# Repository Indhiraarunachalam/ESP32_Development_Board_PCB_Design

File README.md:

# ESP32 Development Board PCB Design

## Overview

This project presents the design of a custom ESP32 Development Board PCB developed using KiCad. The board includes USB connectivity, a regulated 3.3V power supply, reset and boot circuits, and a DHT22 temperature and humidity sensor interface. The design follows the complete PCB development workflow from schematic capture to PCB layout and Gerber generation.

---

## Features

- ESP32 Development Board
- DHT22 Temperature & Humidity Sensor Interface
- USB Power Input
- 3.3V Voltage Regulator
- Reset (EN) Button
- Boot Button
- Status LED
- Two-Layer PCB Design

---

## Software Used

- KiCad

---

## Hardware Components

- ESP32-WROOM Module
- DHT22 Sensor
- USB Connector
- AMS1117-3.3V Voltage Regulator
- Push Buttons
- LEDs
- Resistors
- Capacitors
- Transistor

---

## Design Flow

1. Schematic Design
2. ERC Verification
3. PCB Layout
4. Component Placement
5. Routing
6. DRC Verification
7. Gerber Generation

---

## Design Verification

- ERC Passed ✅
- DRC Passed ✅
- Gerber Files Generated Successfully ✅
- Ready for PCB Fabrication ✅

---

## Repository Structure

```
ESP32-Development-Board-PCB-Design
│
├── ESP32_DHT.kicad_sch
├── ESP32_DHT.kicad_pcb
├── README.md
│
├── Gerber/
│
└── Images/
    ├── Schematic.png
    ├── PCB_Toplayer.png
    └── PCB_Bottomlayer.png
```

---

## Project Images

### Schematic

### PCB Layout - Top Layer

### PCB Layout - Bottom Layer

---

## Author

**Indhira A**

Electronics and Communication Engineering Student

Interested in PCB Design, Embedded Systems and IoT.

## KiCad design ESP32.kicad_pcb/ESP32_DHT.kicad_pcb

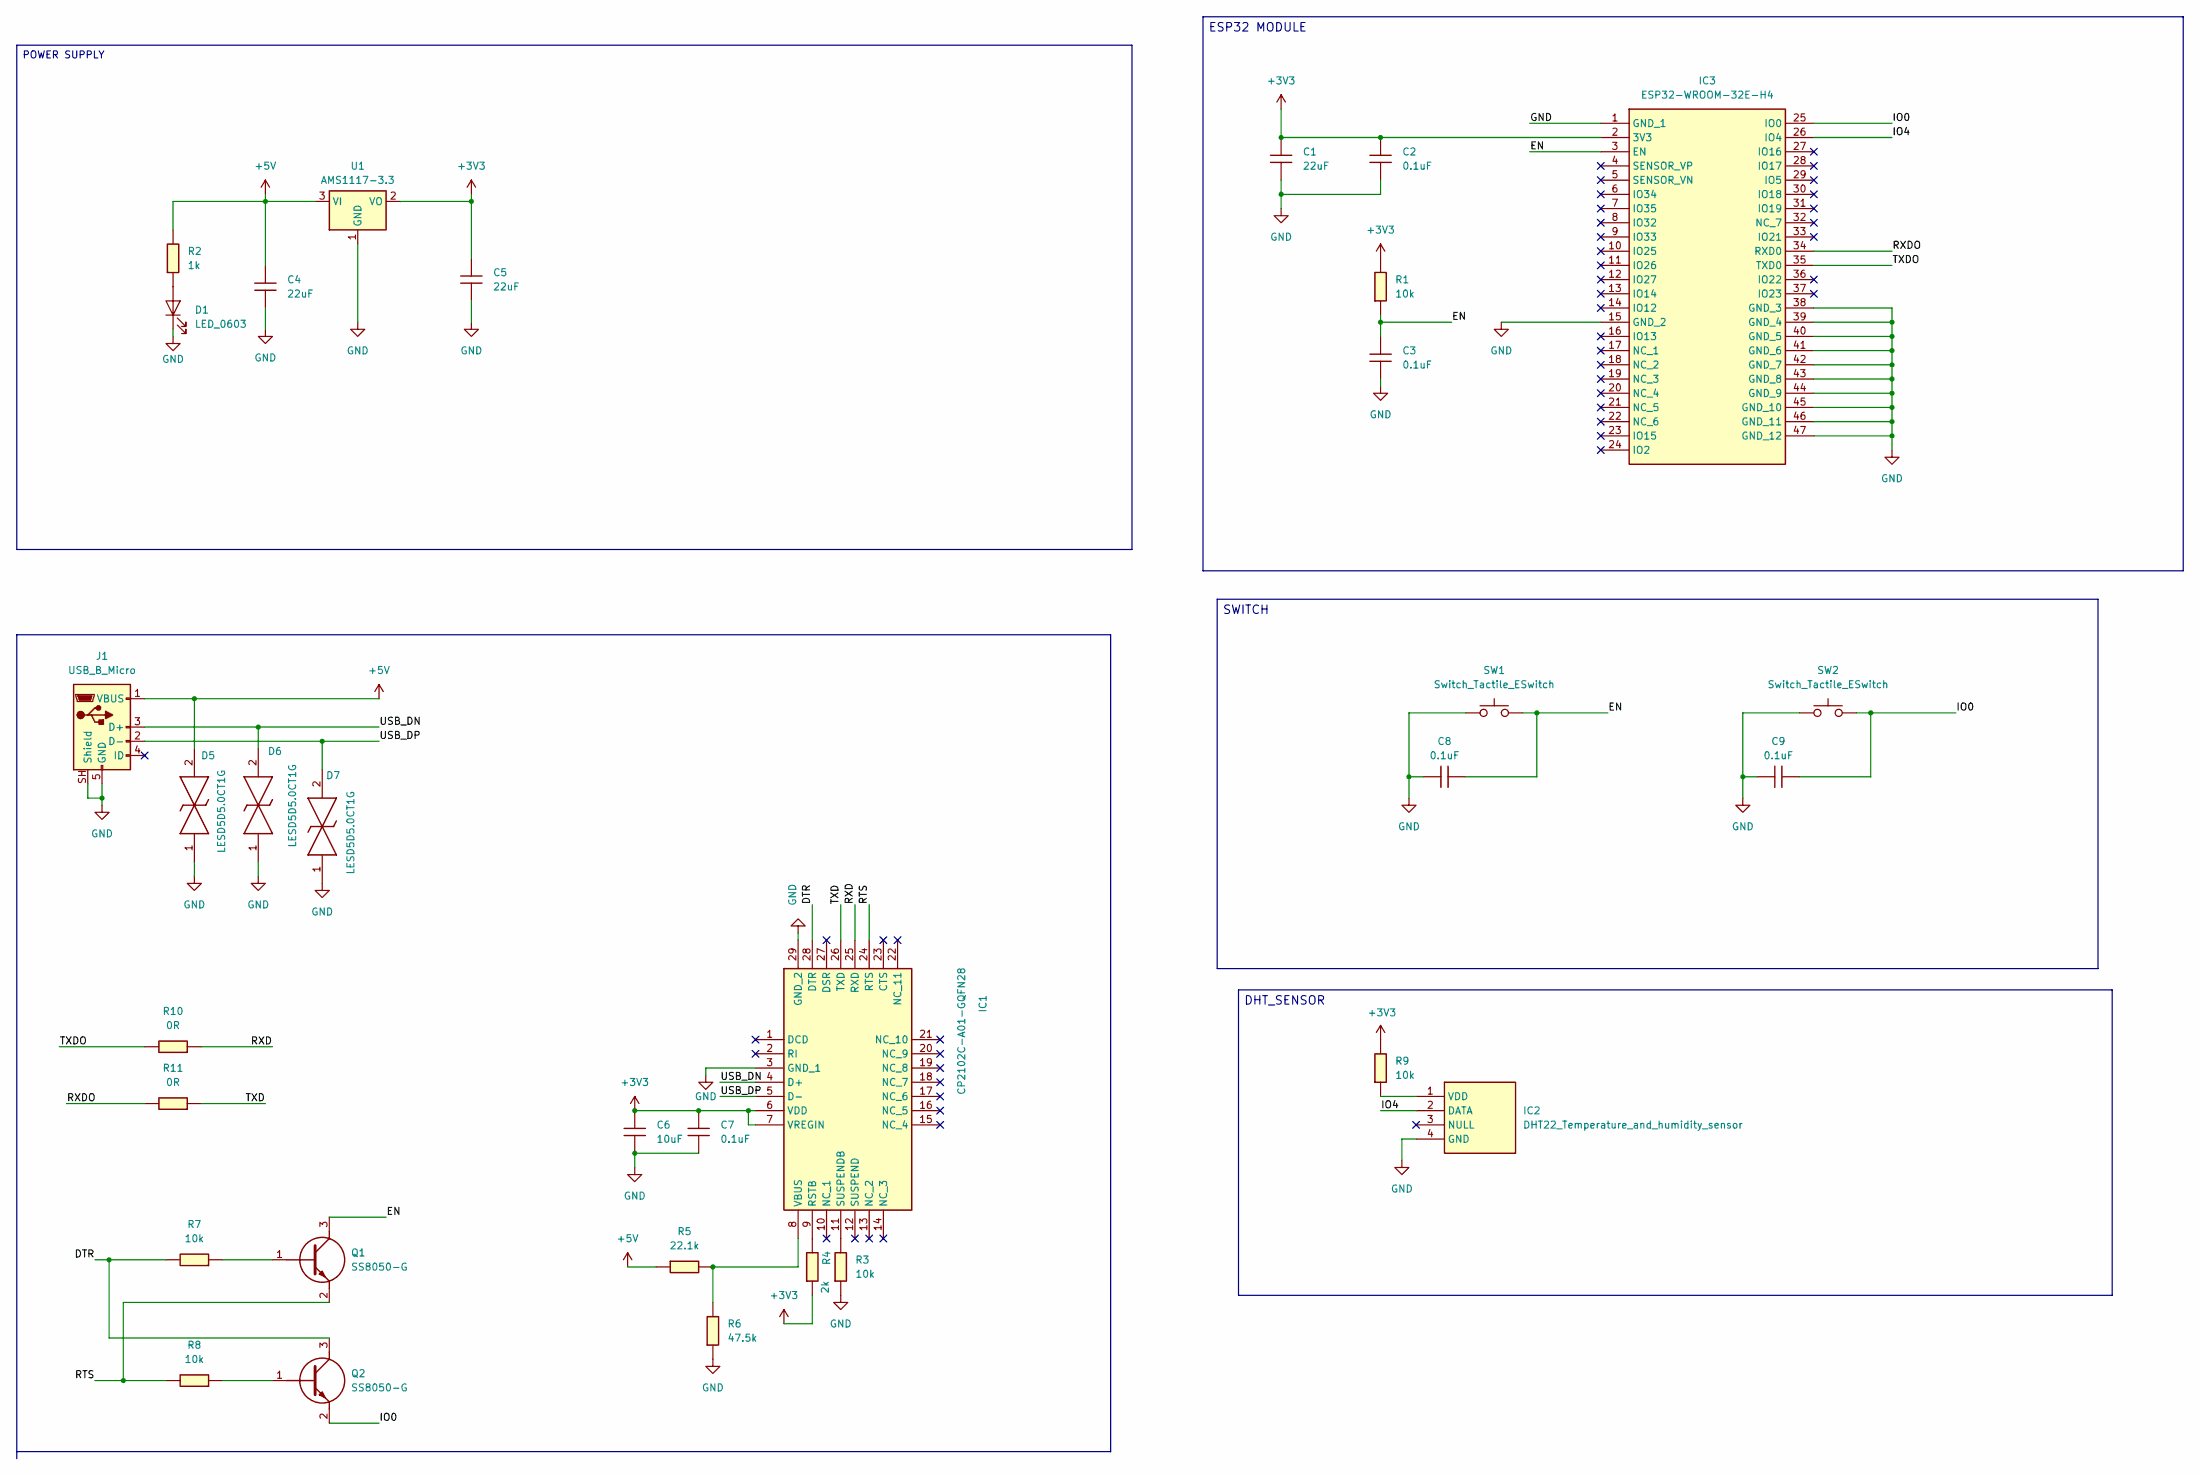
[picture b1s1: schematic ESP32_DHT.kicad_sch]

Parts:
C1, C4, C5: 22uF; C_0603
C2, C3, C7, C8, C9: 0.1uF; C_0603
C6: 10uF; C_0603
D1: LED_0603
D5, D6, D7: LESD5D5.0CT1G; LESD5D50CT1G; Manufacturer_Part_Number LESD5D5.0CT1G
IC1: CP2102C-A01-GQFN28; QFN50P500X500X80-29N-D; Mouser Part Number 634-P2102CA01GQFN28
IC2: DHT22_Temperature_and_humidity_sensor; DHT22Temperatureandhumiditysensor; Manufacturer_Part_Number DHT22 Temperature and humidity sensor
IC3: ESP32-WROOM-32E-H4; ESP32WROOM32EH4; Manufacturer_Part_Number ESP32-WROOM-32E-H4; Mouser Part Number 356-ESP32WRM320EH3PS
J1: USB_B_Micro; USB_Micro-B_Molex-105017-0001
Q1, Q2: SS8050-G; SOT95P240X115-3N; Manufacturer_Part_Number SS8050-G; Mouser Part Number 750-SS8050-G
R1, R3, R7, R8, R9: 10k; R_0603
R2: 1k; R_0603
R4: 2k; R_0603
R5: 22.1k; R_0603
R6: 47.5k; R_0603
R10, R11: 0R; R_0603
SW1, SW2: Switch_Tactile_ESwitch; Button_ESwitch_TL3315NF100Q_4.5x4.5mm
U1: AMS1117-3.3; SOT-223-3_TabPin2

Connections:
+3V3: C1.1, C2.1, C5.1, C6.1, C7.1, IC1.6 (VDD), IC1.7 (VREGIN), IC3.2 (3V3), R1.1, R4.2, R9.1, U1.2 (VO)
+5V: C4.1, D5.2, J1.1 (VBUS), R2.1, R5.2, U1.3 (VI)
/DTR: IC1.28 (DTR), Q2.3 (C), R7.1
/EN: C3.1, C8.2, IC3.3 (EN), Q1.3 (C), R1.2, SW1.3, SW1.4
/IO0: C9.2, IC3.25 (IO0), Q2.2 (E), SW2.3, SW2.4
/IO4: IC2.2 (DATA), IC3.26 (IO4)
/RTS: IC1.24 (RTS), Q1.2 (E), R8.1
/RXD: IC1.25 (RXD), R10.2
/RXDO: IC3.34 (RXD0), R11.1
/TXD: IC1.26 (TXD), R11.2
/TXDO: IC3.35 (TXD0), R10.1
/USB_DN: D6.2, IC1.4 (D+), J1.3 (D+)
/USB_DP: D7.2, IC1.5 (D-), J1.2 (D-)
GND: C1.2, C2.2, C3.2, C4.2, C5.2, C6.2, C7.2, C8.1, C9.1, D1.1 (K), D5.1, D6.1, D7.1, IC1.3 (GND_1), IC1.29 (GND_2), IC2.4 (GND), IC3.1 (GND_1), IC3.15 (GND_2), IC3.38 (GND_3), IC3.39 (GND_4), IC3.40 (GND_5), IC3.41 (GND_6), IC3.42 (GND_7), IC3.43 (GND_8), IC3.44 (GND_9), IC3.45 (GND_10), IC3.46 (GND_11), IC3.47 (GND_12), J1.5 (GND), J1.SH (Shield), R3.2, R6.2, SW1.1, SW1.2, SW2.1, SW2.2, U1.1 (GND)
unnamed: D1.2 (A), R2.2
unnamed: IC1.9 (RSTB), R4.1
unnamed: IC1.11 (SUSPENDB), R3.1
unnamed: IC1.8 (VBUS), R5.1, R6.1
unnamed: IC2.1 (VDD), R9.2
unnamed: Q1.1 (B), R7.2
unnamed: Q2.1 (B), R8.2

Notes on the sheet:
SWITCH
ESP32 MODULE
DHT_SENSOR
POWER SUPPLY

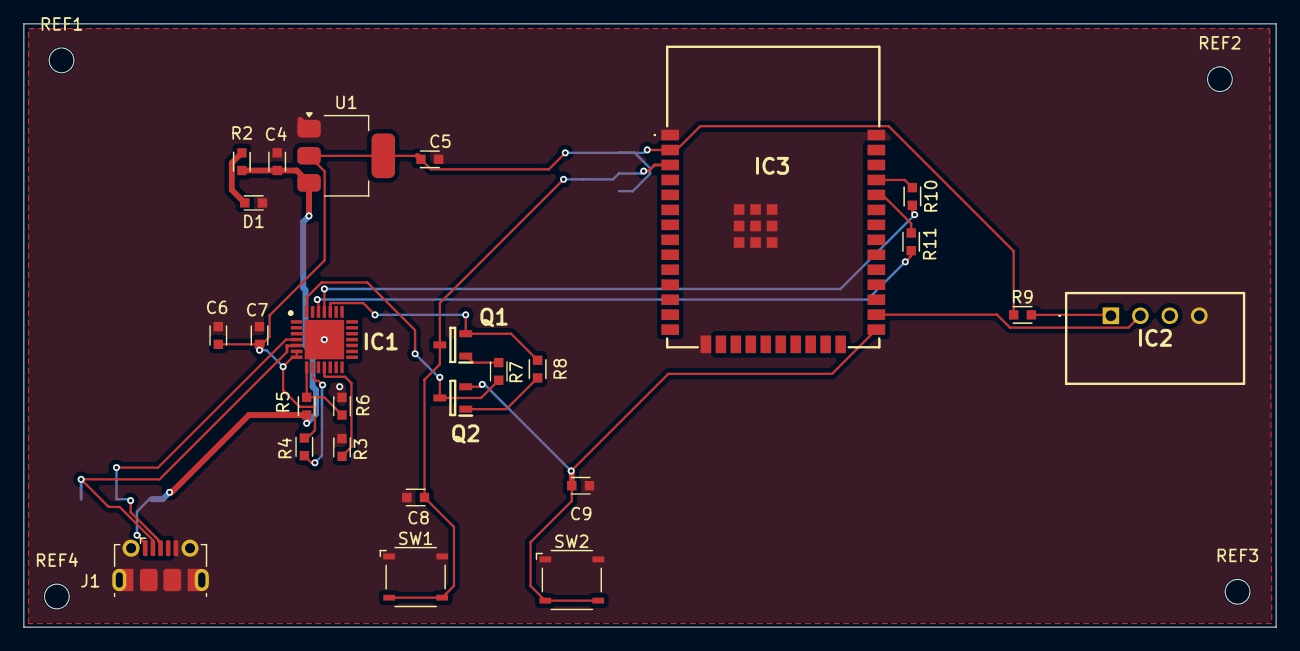
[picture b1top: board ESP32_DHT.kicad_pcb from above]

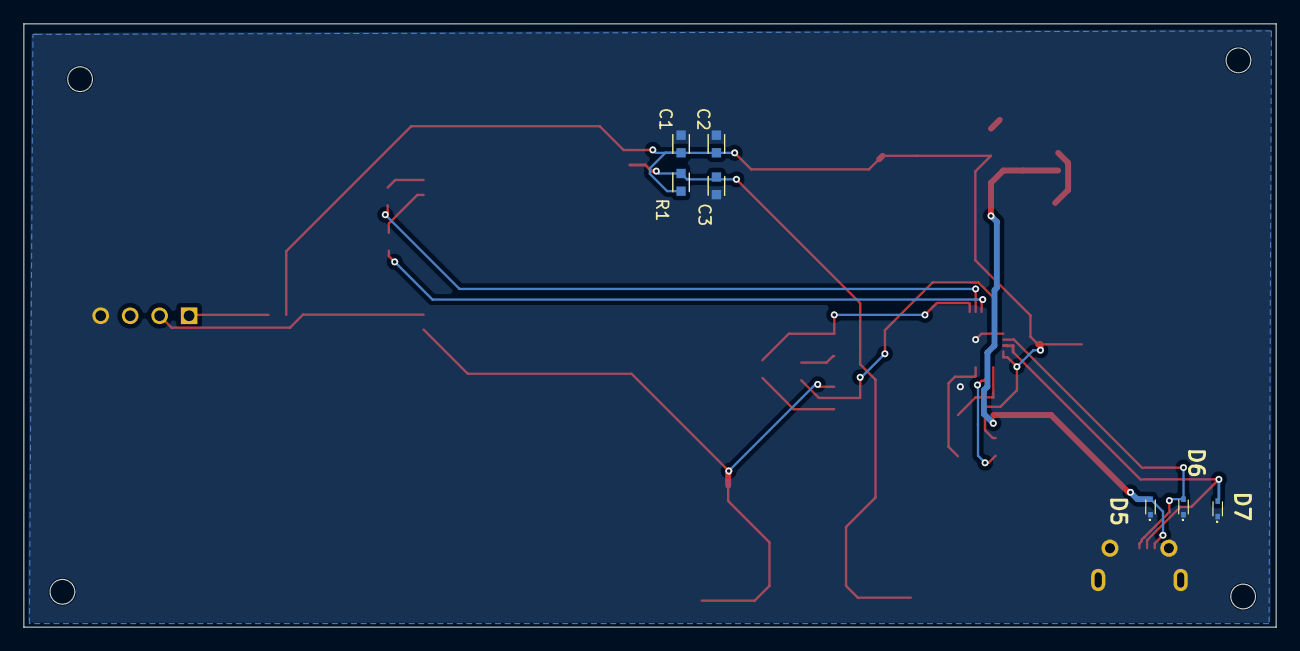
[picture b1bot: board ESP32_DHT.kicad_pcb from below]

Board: 2 copper layers, 106.3 x 51.2 mm, 37 parts (7 on the bottom side), 21 nets.

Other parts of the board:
REF1, REF2, REF3, REF4: MountingHole_2.1mm
